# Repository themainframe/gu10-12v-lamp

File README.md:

# `gu10-12v-lamp`

This is a [GU10](https://en.wikipedia.org/wiki/Bi-pin_lamp_base#Types) style lamp for **12V** use, ideal for situations where a mains lighting system has been converted to 12V. The driverless design makes them compatible with PWM-based or voltage-based dimming. An integral diode bridge allows insertion in either orientation. They are made with standard FR4 PCB rather than Aluminium for lower cost.

This is a KiCad (5.1.9-0-10_14) project.

Gerbers, schematic & BOM may be found in the `outputs` directory.

After production, a sandwich of **M3** 30mm (or shorter/longer, depending on your fitting depth) standard cap-head machine screws, bolts and washers can be fitted through the central holes to produce GU10 compatible "lugs" for insertion into a standard GU10 bayonet lamp holder.

For outdoor use I'd suggest conformally coating the boards on the top and bottom sides _after_ insertion of the M3 fasteners.

**These lamps are for 12V DC only. Do not connect these lamps to mains voltage.**

Standard 2835 LED chips are used (I used 3000K 150mA 2.95Vf [CREE J Series® JB2835AWT-W-U30GA0000-N0000001](https://www.digikey.co.uk/en/products/detail/cree-inc/JB2835AWT-W-U30GA0000-N0000001/10820387)). LEDs are in 4 groups of (3 chips in series) with a resistor for each group, with each group seeing a ~11V supply voltage after the diode bridge drop. I'd recommend using 39Ω 2512-size resistors (for a LED current of 50mA) and a total system current of 200mA (~2.4W including power dissipated by the diode bridge). The lamps stay at a sensible temperature at this power.

## Revisions

* **Issue A** - Initial release (used in the example photos above).
* **Issue B** - Improved layout for better thermals.

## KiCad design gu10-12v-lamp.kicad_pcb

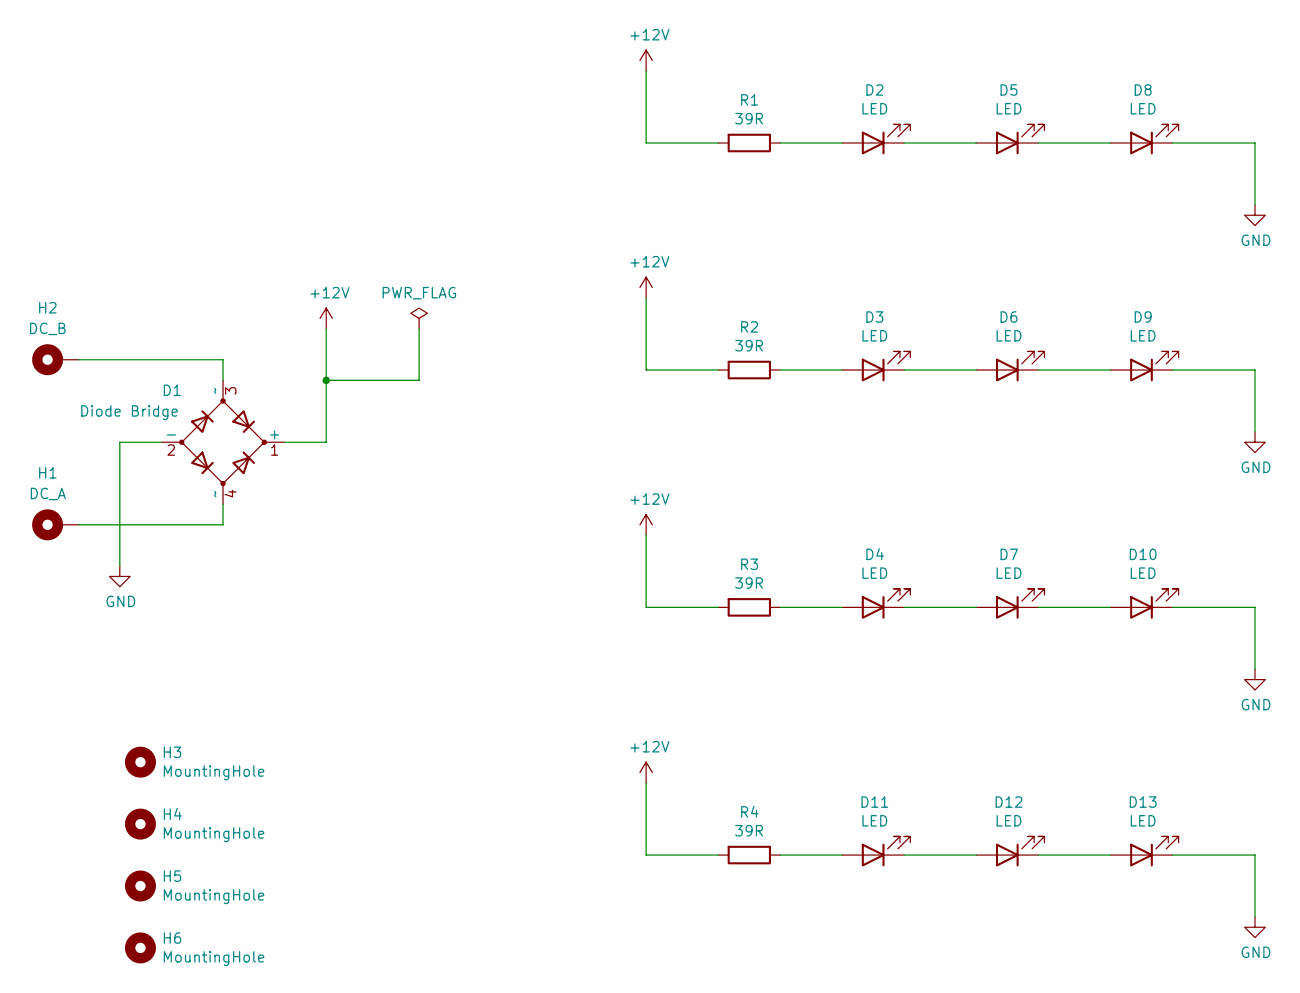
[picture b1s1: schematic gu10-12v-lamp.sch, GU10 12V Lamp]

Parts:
D1: Diode Bridge; Diode_Bridge_Vishay_DFS
D2, D3, D4, D5, D6, D7, D8, D9, D10, D11, D12, D13: LED; LED_PLCC_2835
H1: DC_A; MountingHole_3.2mm_M3_Pad_Via
H2: DC_B; MountingHole_3.2mm_M3_Pad_Via
H3, H4, H5, H6: MountingHole; MountingHole_2.5mm
R1, R2, R3, R4: 39R; R_2512_6332Metric

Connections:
+12V: D1.1 (+), R1.2, R2.2, R3.2, R4.2
GND: D1.2 (-), D8.1 (K), D9.1 (K), D10.1 (K), D13.1 (K)
unnamed: D1.3 (~~), H2.1
unnamed: D1.4 (~~), H1.1
unnamed: D2.1 (K), D5.2 (A)
unnamed: D2.2 (A), R1.1
unnamed: D3.1 (K), D6.2 (A)
unnamed: D3.2 (A), R2.1
unnamed: D4.1 (K), D7.2 (A)
unnamed: D4.2 (A), R3.1
unnamed: D5.1 (K), D8.2 (A)
unnamed: D6.1 (K), D9.2 (A)
unnamed: D7.1 (K), D10.2 (A)
unnamed: D11.1 (K), D12.2 (A)
unnamed: D11.2 (A), R4.1
unnamed: D12.1 (K), D13.2 (A)

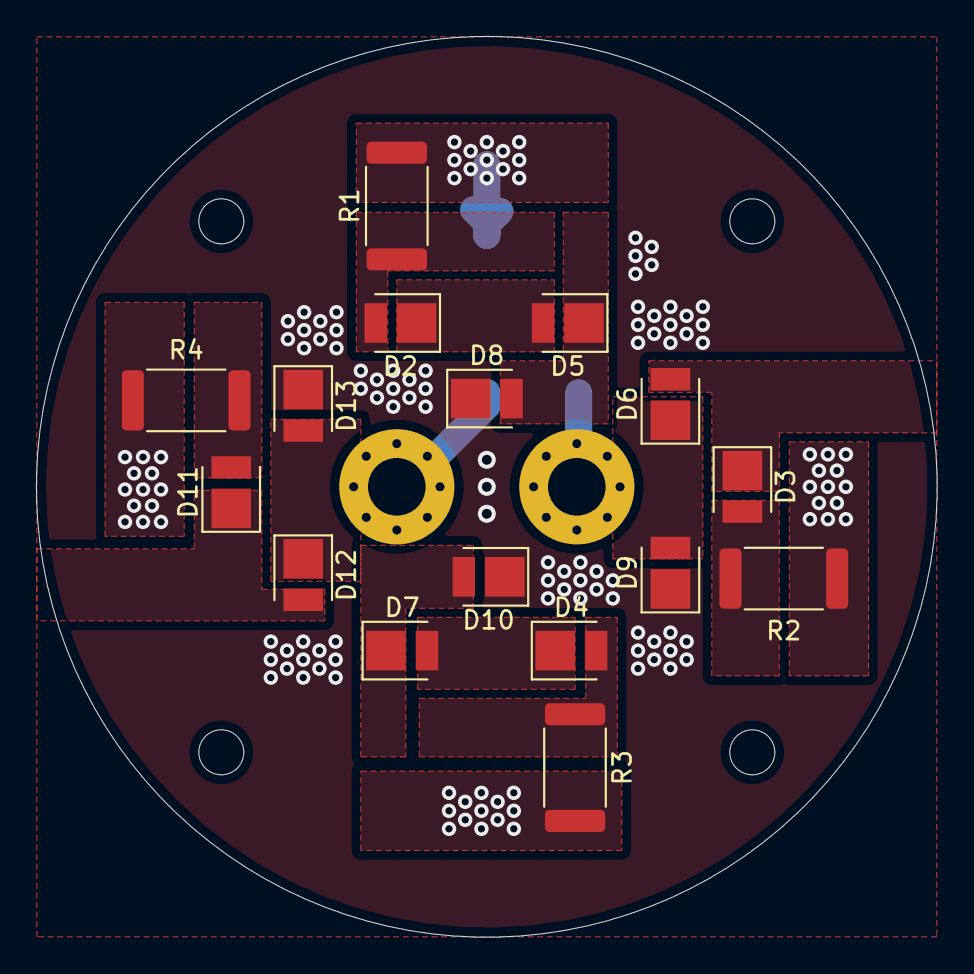
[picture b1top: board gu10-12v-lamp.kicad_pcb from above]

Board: 2 copper layers, 50.0 x 50.0 mm, 23 parts (1 on the bottom side), 16 nets.

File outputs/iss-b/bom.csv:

Component,Description,Part,References,Value,Footprint,Quantity Per PCB,Datasheet,Vendor 10of GBP,Vendor,Vendor SKU
1,"Diode bridge, +ve/-ve/AC/AC",D_Bridge_+-AA,D1,Diode Bridge,Diode_Bridge_Vishay_DFS,1,~,0.41,Digi-Key,DF01SA-E3/77GICT-ND
2,Light emitting diode,LED,D2 D3 D4 D5 D6 D7 D8 D9 D10 D11 D12 D13,LED,LED_PLCC_2835,12,~,0.01500,Digi-Key,2138-JB2835AWT-W-U30GA0000-N0000001CT-ND
3,Resistor,R,R1 R2 R3 R4,39R,R_2512_6332Metric,4,~,0.181,Digi-Key,RMCF2512JT39R0CT-ND





Component Groups:,3
Component Count:,17
Fitted Components:,17
Number of PCBs:,1
Total components:,17
Schematic Version:,ISS B
Schematic Date:,
PCB Variant:,udefault
BoM Date:,"Monday, 16 August 2021 at 18:13:15"
Schematic Source:,gu10-12v-lamp.sch
KiCad Version:,Eeschema (5.1.9-0-10_14)

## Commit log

2021-06-06 Add: Initial Commit
2021-08-05 Add: Gerber files
2021-08-05 Add: Issue B assets
2021-08-05 Add: License
2021-08-05 Fix: Remove white background from example images
2021-08-05 Fix: Remove background from example images
2021-08-05 Fix: Power calcs
2021-08-16 Add: BOM
